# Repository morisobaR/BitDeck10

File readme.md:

# BitDeck10

## Overview

BitDeck10 is a 5x2 keys + 1 rotary encoder macro keyboard with OLED.

<a href="doc/readme.md">Build Guide</a> (Japanese only)

The design of the rotary encoder is based on the THQWGD001C created by Taro Hayashi.<br/>
https://github.com/Taro-Hayashi/THQWGD001

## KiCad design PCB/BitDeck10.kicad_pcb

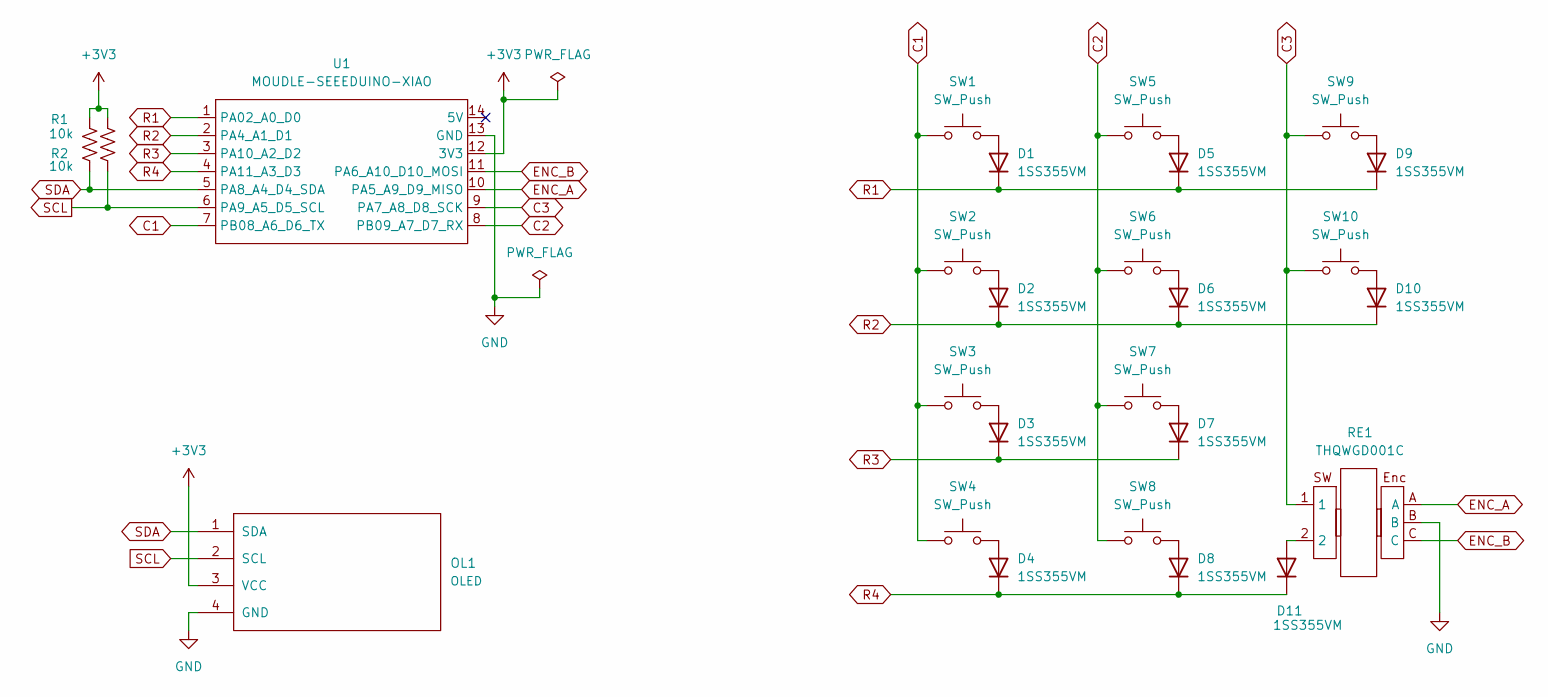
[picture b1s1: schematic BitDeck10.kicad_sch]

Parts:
D1, D2, D3, D4, D5, D6, D7, D8, D9, D10, D11: 1SS355VM; D3_TH_SMD_v2
OL1: OLED; OLED_v2
R1, R2: 10k; R_0603_1608Metric_Pad0.98x0.95mm_HandSolder
RE1: THQWGD001C; THQWGD001C [4pin] [Reversible]
SW1, SW2, SW3, SW4, SW5, SW6, SW7, SW8, SW9, SW10: SW_Push; CherryMX_Hotswap
U1: MOUDLE-SEEEDUINO-XIAO; MOUDLE14P-SMD-2.54-21X17.8MM_SMD_THT

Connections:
+3V3: OL1.3 (VCC), R1.1, R2.1, U1.12 (3V3); also elsewhere on the board
C1: SW1.1, SW2.1, SW3.1, SW4.1, U1.7 (PB08_A6_D6_TX)
C2: SW5.1, SW6.1, SW7.1, SW8.1, U1.8 (PB09_A7_D7_RX)
C3: RE1.1, SW9.1, SW10.1, U1.9 (PA7_A8_D8_SCK)
ENC_A: RE1.A, U1.10 (PA5_A9_D9_MISO)
ENC_B: RE1.C, U1.11 (PA6_A10_D10_MOSI)
GND: OL1.4 (GND), RE1.B, U1.13 (GND)
unnamed: D1.2 (A), SW1.2
unnamed: D2.2 (A), SW2.2
unnamed: D3.2 (A), SW3.2
unnamed: D4.2 (A), SW4.2
unnamed: D5.2 (A), SW5.2
unnamed: D6.2 (A), SW6.2
unnamed: D7.2 (A), SW7.2
unnamed: D8.2 (A), SW8.2
unnamed: D9.2 (A), SW9.2
unnamed: D10.2 (A), SW10.2
unnamed: D11.2 (A), RE1.2
R1: D1.1 (K), D5.1 (K), D9.1 (K), U1.1 (PA02_A0_D0)
R2: D2.1 (K), D6.1 (K), D10.1 (K), U1.2 (PA4_A1_D1)
R3: D3.1 (K), D7.1 (K), U1.3 (PA10_A2_D2)
R4: D4.1 (K), D8.1 (K), D11.1 (K), U1.4 (PA11_A3_D3)
SCL: OL1.2 (SCL), R2.2, U1.6 (PA9_A5_D5_SCL); also elsewhere on the board
SDA: OL1.1 (SDA), R1.2, U1.5 (PA8_A4_D4_SDA); also elsewhere on the board

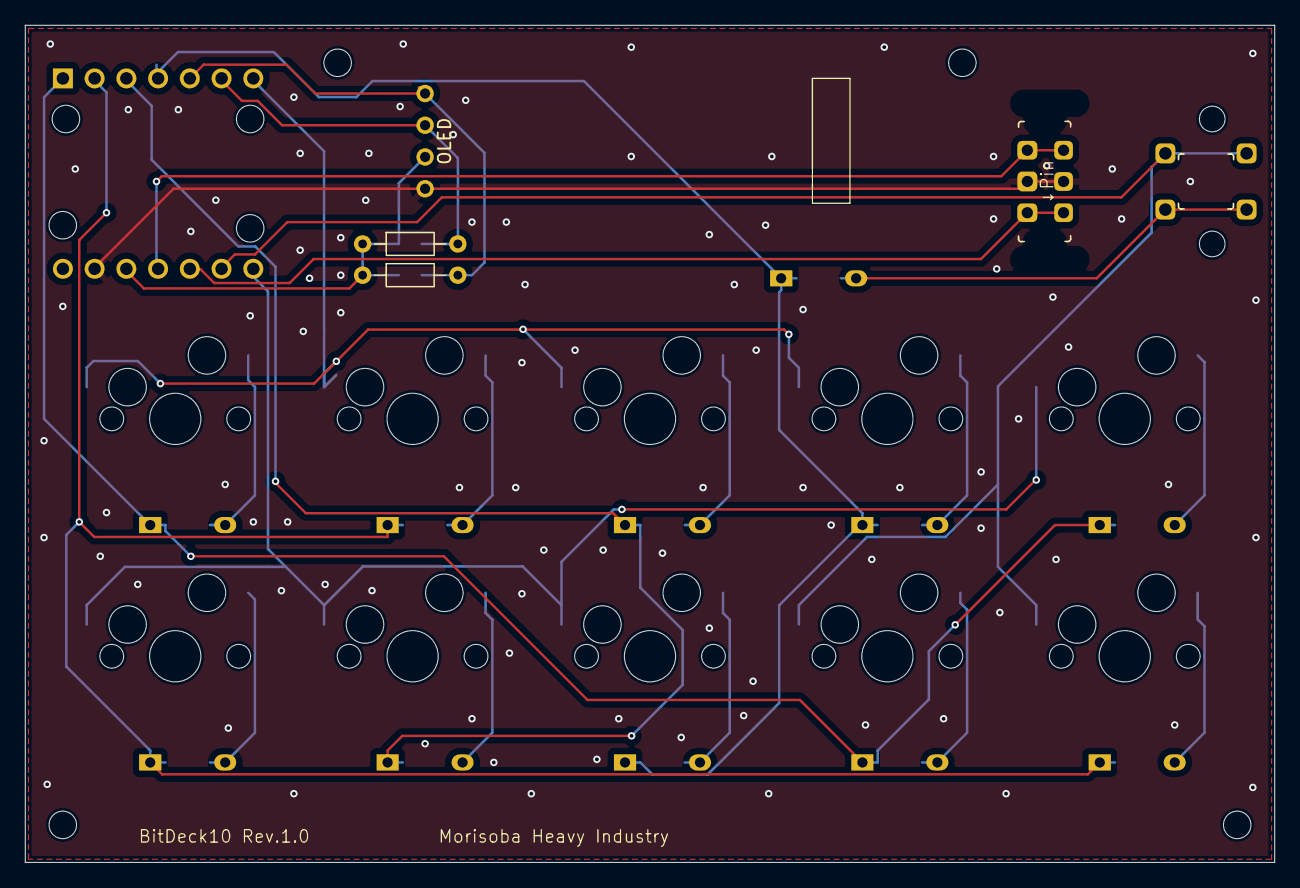
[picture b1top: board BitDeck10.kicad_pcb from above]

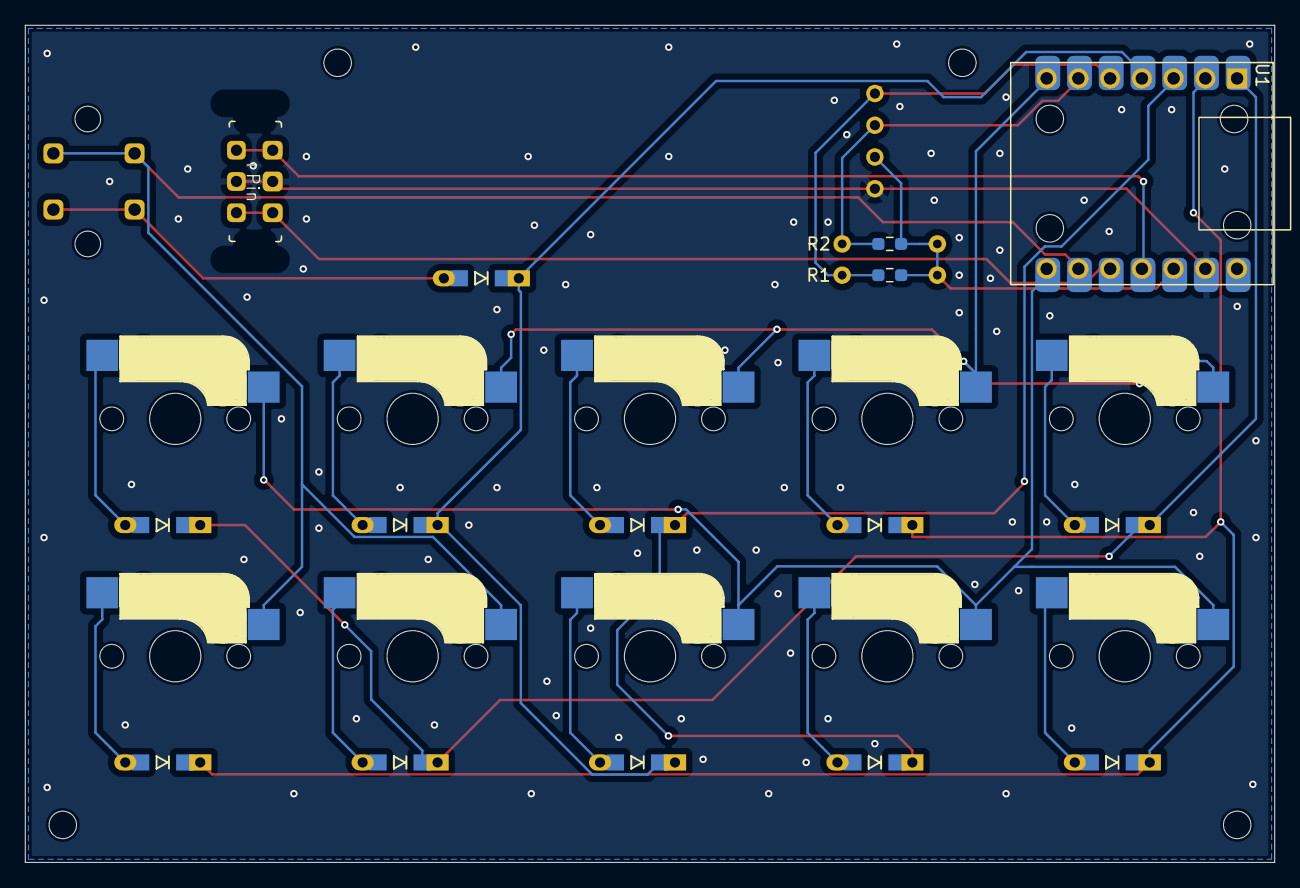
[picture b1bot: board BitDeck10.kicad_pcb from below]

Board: 2 copper layers, 100.0 x 67.0 mm, 36 parts (14 on the bottom side), 24 nets.

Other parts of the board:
R3, R4: R_Axial_DIN0204_L3.6mm_D1.6mm_P7.62mm_Horizontal
REF01, REF02, REF03, REF04, REF05, REF06, REF07, REF08: MountingHole_2.2mm_M2_DIN965

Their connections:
+3V3: R3.1, R4.1; also elsewhere on the board
SCL: R4.2; also elsewhere on the board
SDA: R3.2; also elsewhere on the board

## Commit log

2026-05-05 QMK FirmwareへのPR対応
2026-05-05 ビルドガイド追加
2026-05-05 typo
2026-05-05 ボトムケースにリブを追加
2026-05-06 ビルドガイド微修正
